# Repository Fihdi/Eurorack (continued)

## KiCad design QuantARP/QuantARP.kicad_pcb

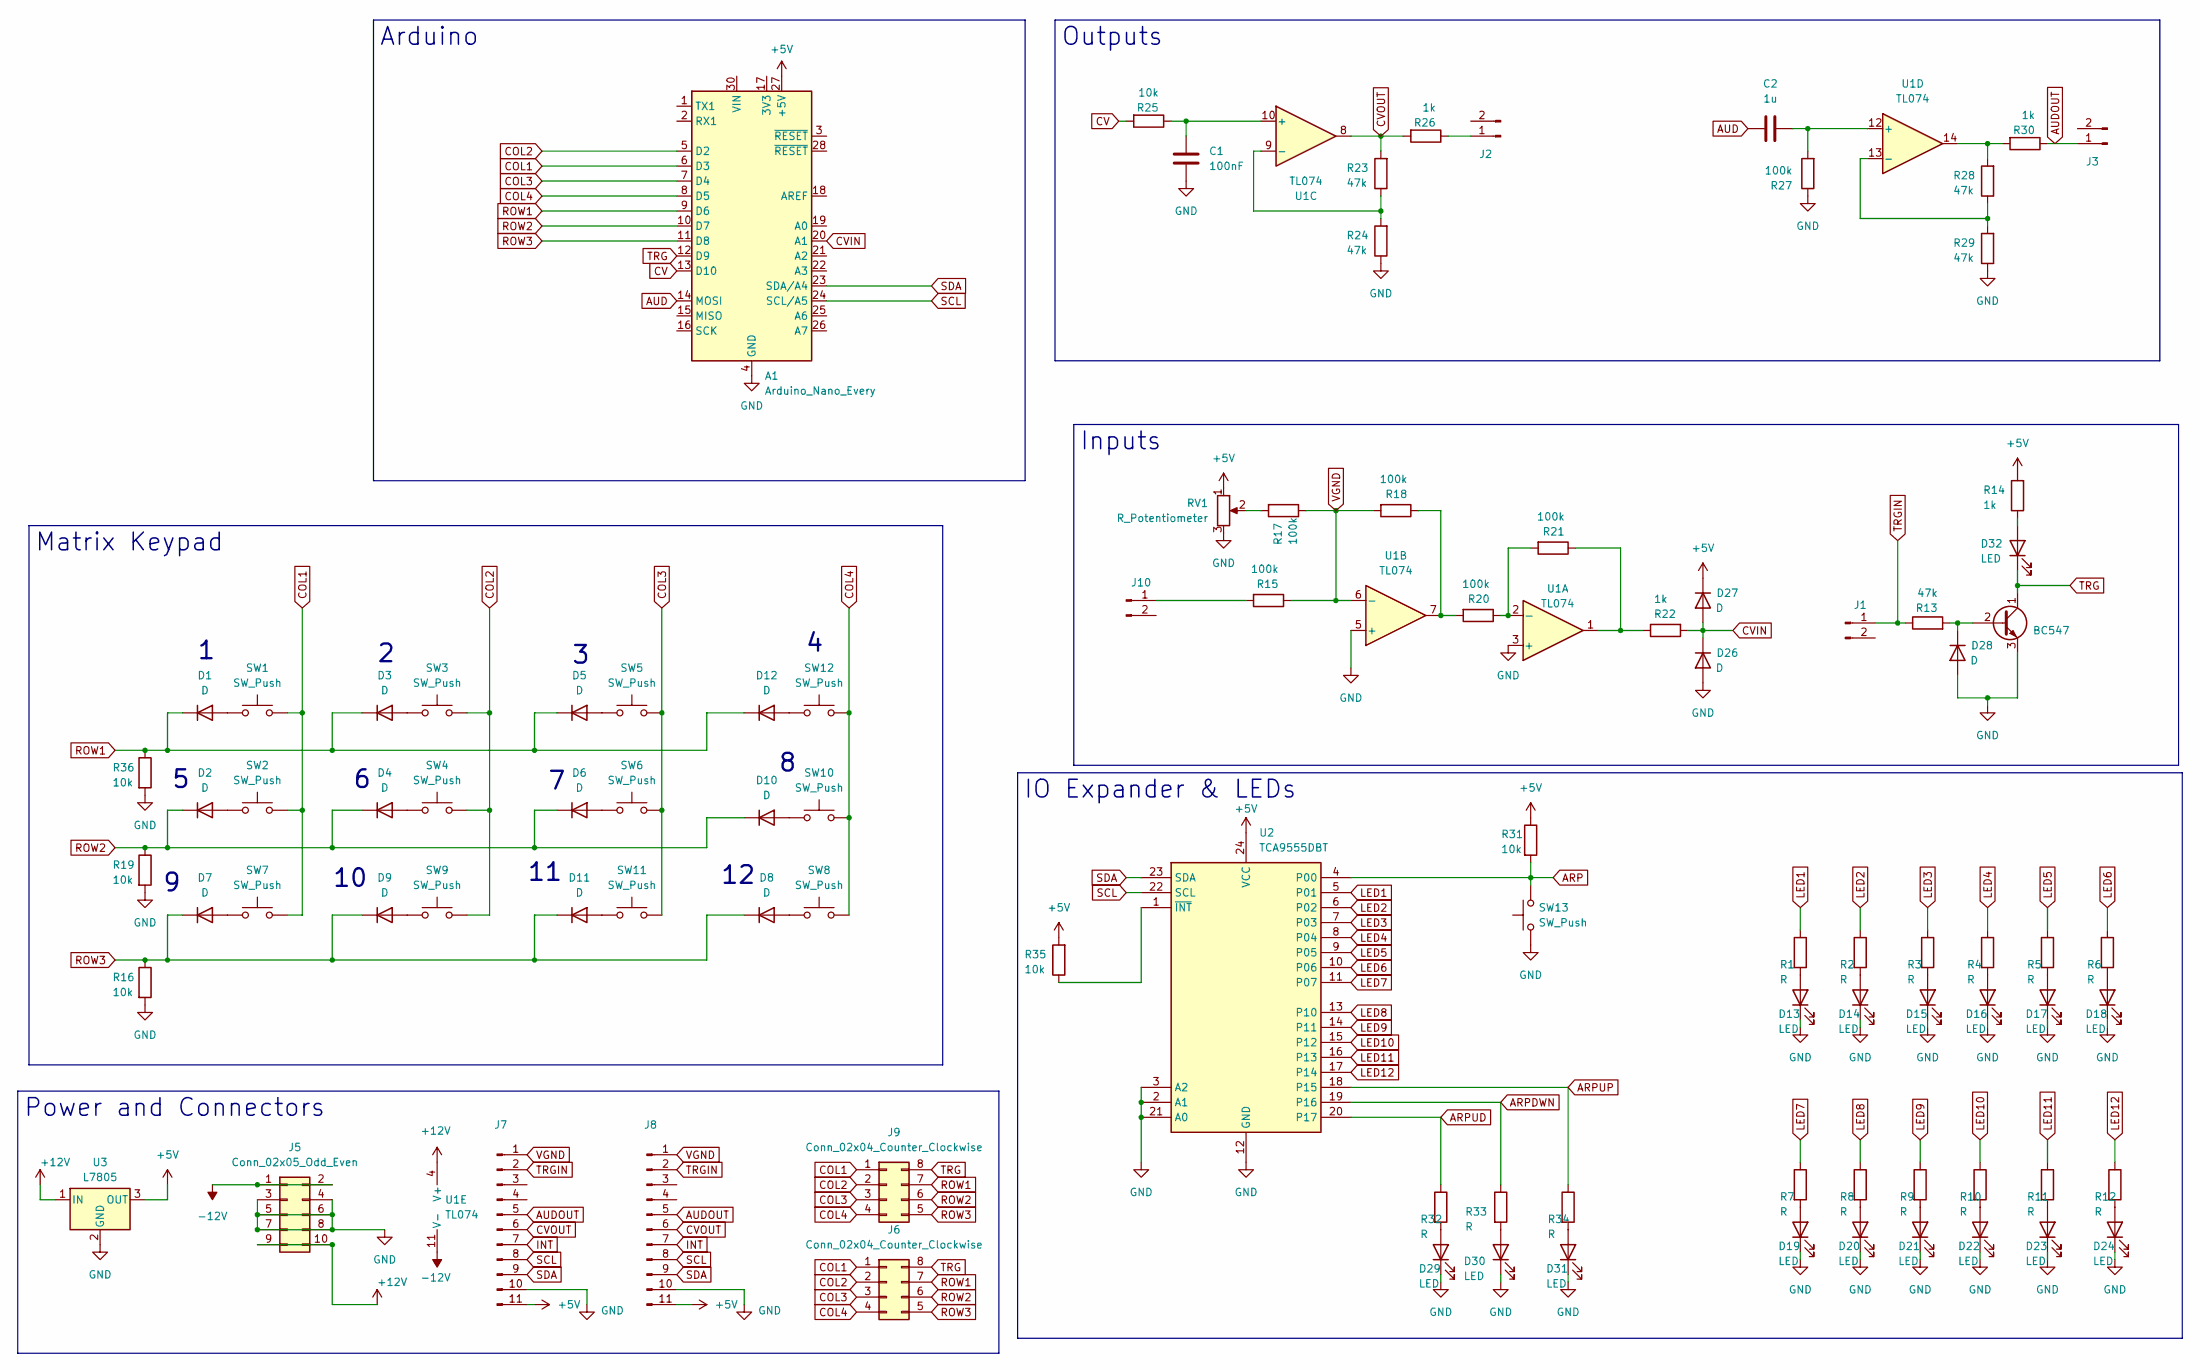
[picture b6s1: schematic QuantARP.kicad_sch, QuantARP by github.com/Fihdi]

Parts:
A1: Arduino_Nano_Every; Arduino_Nano
C1: 100nF; C_Disc_D7.0mm_W2.5mm_P5.00mm
C2: 1u; C_Disc_D7.0mm_W2.5mm_P5.00mm
D1, D2, D3, D4, D5, D6, D7, D8, D9, D10, D11, D12: D; D_SOD-323_HandSoldering
D13, D14, D15, D16, D17, D18, D19, D20, D21, D22, D23, D24, D29, D30, D31, D32: LED; LED_D3.0mm
D26, D27, D28: D; D_1206_3216Metric
J1, J2, J3, J10: Conn_01x02_Pin; 3mm5 Mono Aux
J5: Conn_02x05_Odd_Even; IDC-Header_2x05_P2.54mm_Vertical
J6, J9: Conn_02x04_Counter_Clockwise; IDC-Header_2x04_P2.54mm_Vertical
J7, J8: Conn_01x11_Pin; PinSocket_1x11_P2.54mm_Vertical
Q9: BC547; TO-92_Inline_Wide
R1, R2, R3, R4, R5, R6, R7, R8, R9, R10, R11, R12: R; R_1206_3216Metric
R13, R23, R24, R28, R29: 47k; R_Axial_DIN0207_L6.3mm_D2.5mm_P7.62mm_Horizontal
R14, R22, R26, R30: 1k; R_Axial_DIN0207_L6.3mm_D2.5mm_P7.62mm_Horizontal
R15, R17, R18, R20, R21, R27: 100k; R_Axial_DIN0207_L6.3mm_D2.5mm_P7.62mm_Horizontal
R16, R19, R25, R31, R35, R36: 10k; R_Axial_DIN0207_L6.3mm_D2.5mm_P7.62mm_Horizontal
R32, R33, R34: R; R_Axial_DIN0207_L6.3mm_D2.5mm_P7.62mm_Horizontal
RV1: R_Potentiometer; Potentiometer_Bourns_PTV09A-1_Single_Vertical
SW1, SW2, SW3, SW4, SW5, SW6, SW7, SW8, SW9, SW10, SW11, SW12, SW13: SW_Push; PushButton
U1: TL074; DIP-14_W7.62mm
U2: TCA9555DBT; SSOP-24_5.3x8.2mm_P0.65mm
U3: L7805; TO-252-3_TabPin2

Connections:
+5V: A1.27 (+5V), D27.1 (K), J7.11, J8.11, R14.2, R31.1, R35.2, RV1.1, U2.24 (VCC), U3.3 (OUT)
+12V: J5.9, J5.10, U1.4 (V+), U3.1 (IN)
-12V: J5.1, J5.2, U1.11 (V-)
ARP: R31.2, SW13.2, U2.4 (P00)
ARPDWN: R33.1, U2.19 (P16)
ARPUD: R32.1, U2.20 (P17)
ARPUP: R34.1, U2.18 (P15)
AUD: A1.14 (MOSI), C2.1
AUDOUT: J3.1, J7.5, J8.5, R30.1
COL1: A1.6 (D3), J6.1, J9.1, SW1.2, SW2.2, SW7.2
COL2: A1.5 (D2), J6.2, J9.2, SW3.2, SW4.2, SW9.2
COL3: A1.7 (D4), J6.3, J9.3, SW5.2, SW6.2, SW11.2
COL4: A1.8 (D5), J6.4, J9.4, SW8.2, SW10.2, SW12.2
CV: A1.13 (D10), R25.2
CVIN: A1.20 (A1), D26.1 (K), D27.2 (A), R22.2
CVOUT: J7.6, J8.6, R23.2, R26.2, U1.8
GND: A1.4 (GND), A1.29 (GND), C1.2, D13.1 (K), D14.1 (K), D15.1 (K), D16.1 (K), D17.1 (K), D18.1 (K), D19.1 (K), D20.1 (K), D21.1 (K), D22.1 (K), D23.1 (K), D24.1 (K), D26.2 (A), D28.2 (A), D29.1 (K), D30.1 (K), D31.1 (K), J5.3, J5.4, J5.5, J5.6, J5.7, J5.8, J7.10, J8.10, Q9.3 (E), R16.2, R19.2, R24.1, R27.1, R29.1, R36.2, RV1.3, SW13.1, U1.3 (+), U1.5 (+), U2.2 (A1), U2.3 (A2), U2.12 (GND), U2.21 (A0), U3.2 (GND)
INT: J7.7, J8.7
LED1: R1.1, U2.5 (P01)
LED2: R2.1, U2.6 (P02)
LED3: R3.1, U2.7 (P03)
LED4: R4.1, U2.8 (P04)
LED5: R5.1, U2.9 (P05)
LED6: R6.1, U2.10 (P06)
LED7: R7.1, U2.11 (P07)
LED8: R8.1, U2.13 (P10)
LED9: R9.1, U2.14 (P11)
LED10: R10.1, U2.15 (P12)
LED11: R11.1, U2.16 (P13)
LED12: R12.1, U2.17 (P14)
unnamed: D1.2 (A), SW1.1
unnamed: D2.2 (A), SW2.1
unnamed: D3.2 (A), SW3.1
unnamed: D4.2 (A), SW4.1
unnamed: D5.2 (A), SW5.1
unnamed: D6.2 (A), SW6.1
unnamed: D7.2 (A), SW7.1
unnamed: D8.2 (A), SW8.1
unnamed: D9.2 (A), SW9.1
unnamed: D10.2 (A), SW10.1
unnamed: D11.2 (A), SW11.1
unnamed: D12.2 (A), SW12.1
unnamed: D13.2 (A), R1.2
unnamed: D14.2 (A), R2.2
unnamed: D15.2 (A), R3.2
unnamed: D16.2 (A), R4.2
unnamed: D17.2 (A), R5.2
unnamed: D18.2 (A), R6.2
unnamed: D19.2 (A), R7.2
unnamed: D20.2 (A), R8.2
unnamed: D21.2 (A), R9.2
unnamed: D22.2 (A), R10.2
unnamed: D23.2 (A), R11.2
unnamed: D24.2 (A), R12.2
unnamed: D28.1 (K), Q9.2 (B), R13.2
unnamed: D29.2 (A), R32.2
unnamed: D30.2 (A), R33.2
unnamed: D31.2 (A), R34.2
unnamed: D32.2 (A), R14.1
unnamed: J2.1, R26.1
unnamed: J10.1, R15.2
unnamed: R17.2, RV1.2
unnamed: R18.1, R20.2, U1.7
unnamed: R21.1, R22.1, U1.1
unnamed: R28.2, R30.2, U1.14
unnamed: R20.1, R21.2, U1.2 (-)
unnamed: C1.1, R25.1, U1.10 (+)
unnamed: R23.1, R24.2, U1.9 (-)
unnamed: C2.2, R27.2, U1.12 (+)
unnamed: R28.1, R29.2, U1.13 (-)
unnamed: R35.1, U2.1 (~INT)
ROW1: A1.9 (D6), D1.1 (K), D3.1 (K), D5.1 (K), D12.1 (K), J6.7, J9.7, R36.1
ROW2: A1.10 (D7), D2.1 (K), D4.1 (K), D6.1 (K), D10.1 (K), J6.6, J9.6, R19.1
ROW3: A1.11 (D8), D7.1 (K), D8.1 (K), D9.1 (K), D11.1 (K), J6.5, J9.5, R16.1
TRG: A1.12 (D9), D32.1 (K), J6.8, J9.8, Q9.1 (C)
TRGIN: J1.1, J7.2, J8.2, R13.1
VGND: J7.1, J8.1, R15.1, R17.1, R18.2, U1.6 (-)

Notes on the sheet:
Matrix Keypad
Power and Connectors
Outputs
IO Expander & LEDs
Arduino
Inputs

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
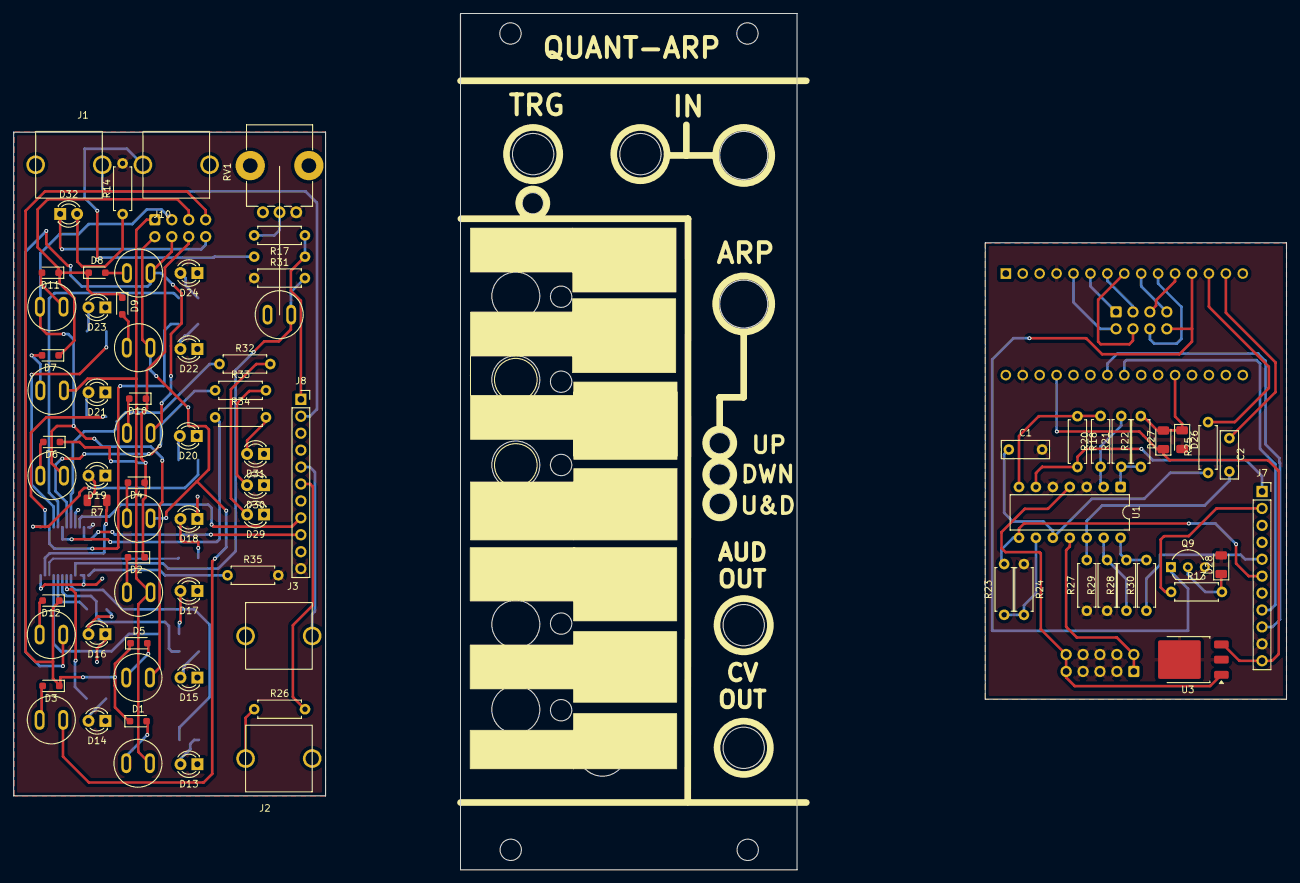
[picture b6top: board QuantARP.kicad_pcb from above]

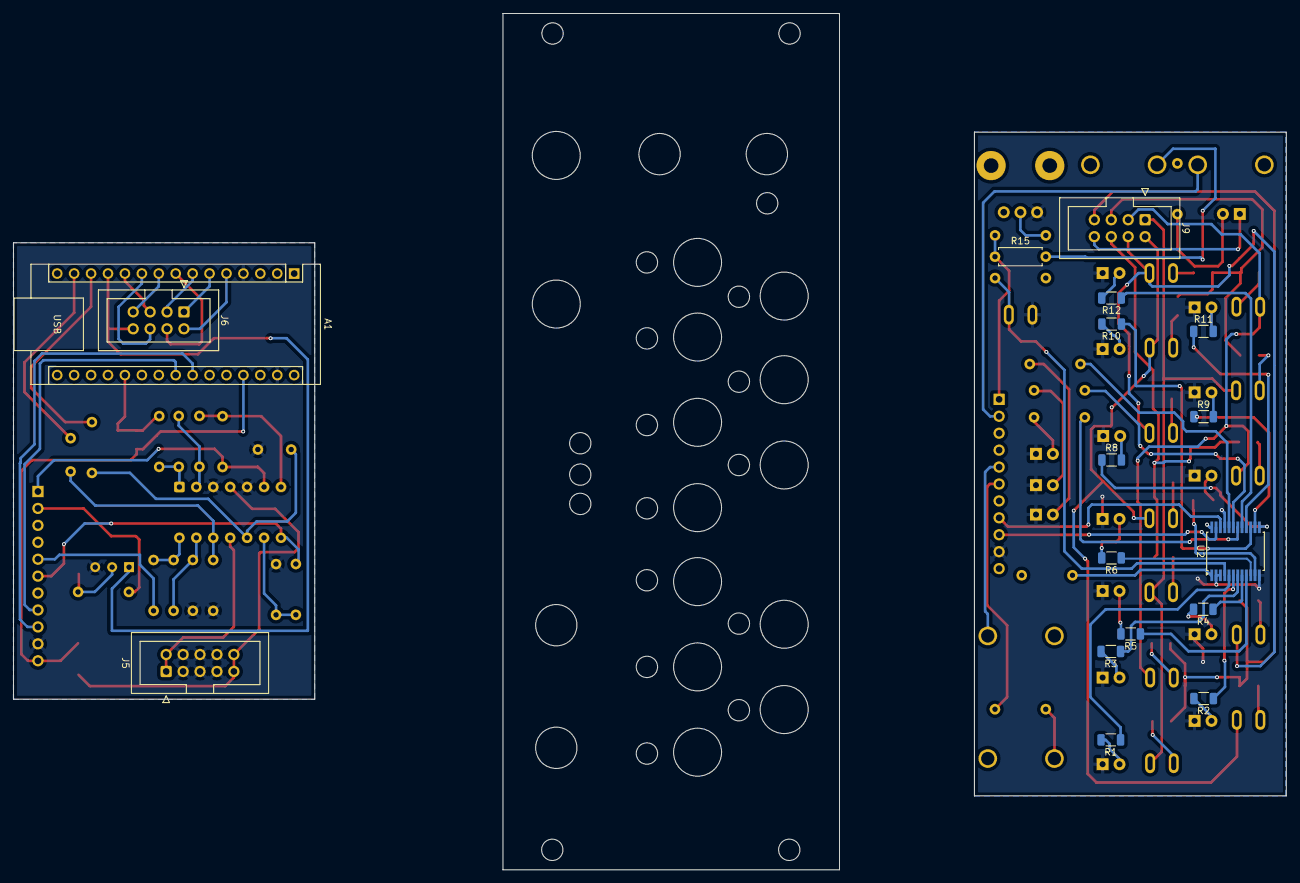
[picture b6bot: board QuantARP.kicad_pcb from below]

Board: 2 copper layers, 191.0 x 128.5 mm, 94 parts (17 on the bottom side), 79 nets.

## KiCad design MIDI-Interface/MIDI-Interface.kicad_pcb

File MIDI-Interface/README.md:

# 8 Channel MIDI interface module in 8hp

MIDI Interface module with 5-Pin MIDI input and with 4 CV and 4 Gate/Trigger outputs. It lets you control other modules with MIDI Controllers or DAWs.

CV channels are mapped to MIDI CC number 20, 21, 22 and 23.

# Expansion

To expand module to 16 channels, the Pin beneath the TL072 can be used to connect two MIDI-INT Modules together. Leave the TL072 unpopulated on the second module and upload MIDI-INT-EXP.ino into the Arduino Nano.

CV channels for the expansion module are mapped to MIDI CC numbers 24, 25, 26 and 27.

Module is inspired by CircuitsAndSounds AutomationSequencer Project and is similar to an Univer Inter from Noise Engineering

https://github.com/CircuitsAndSounds/MIDIAutomationSequencer

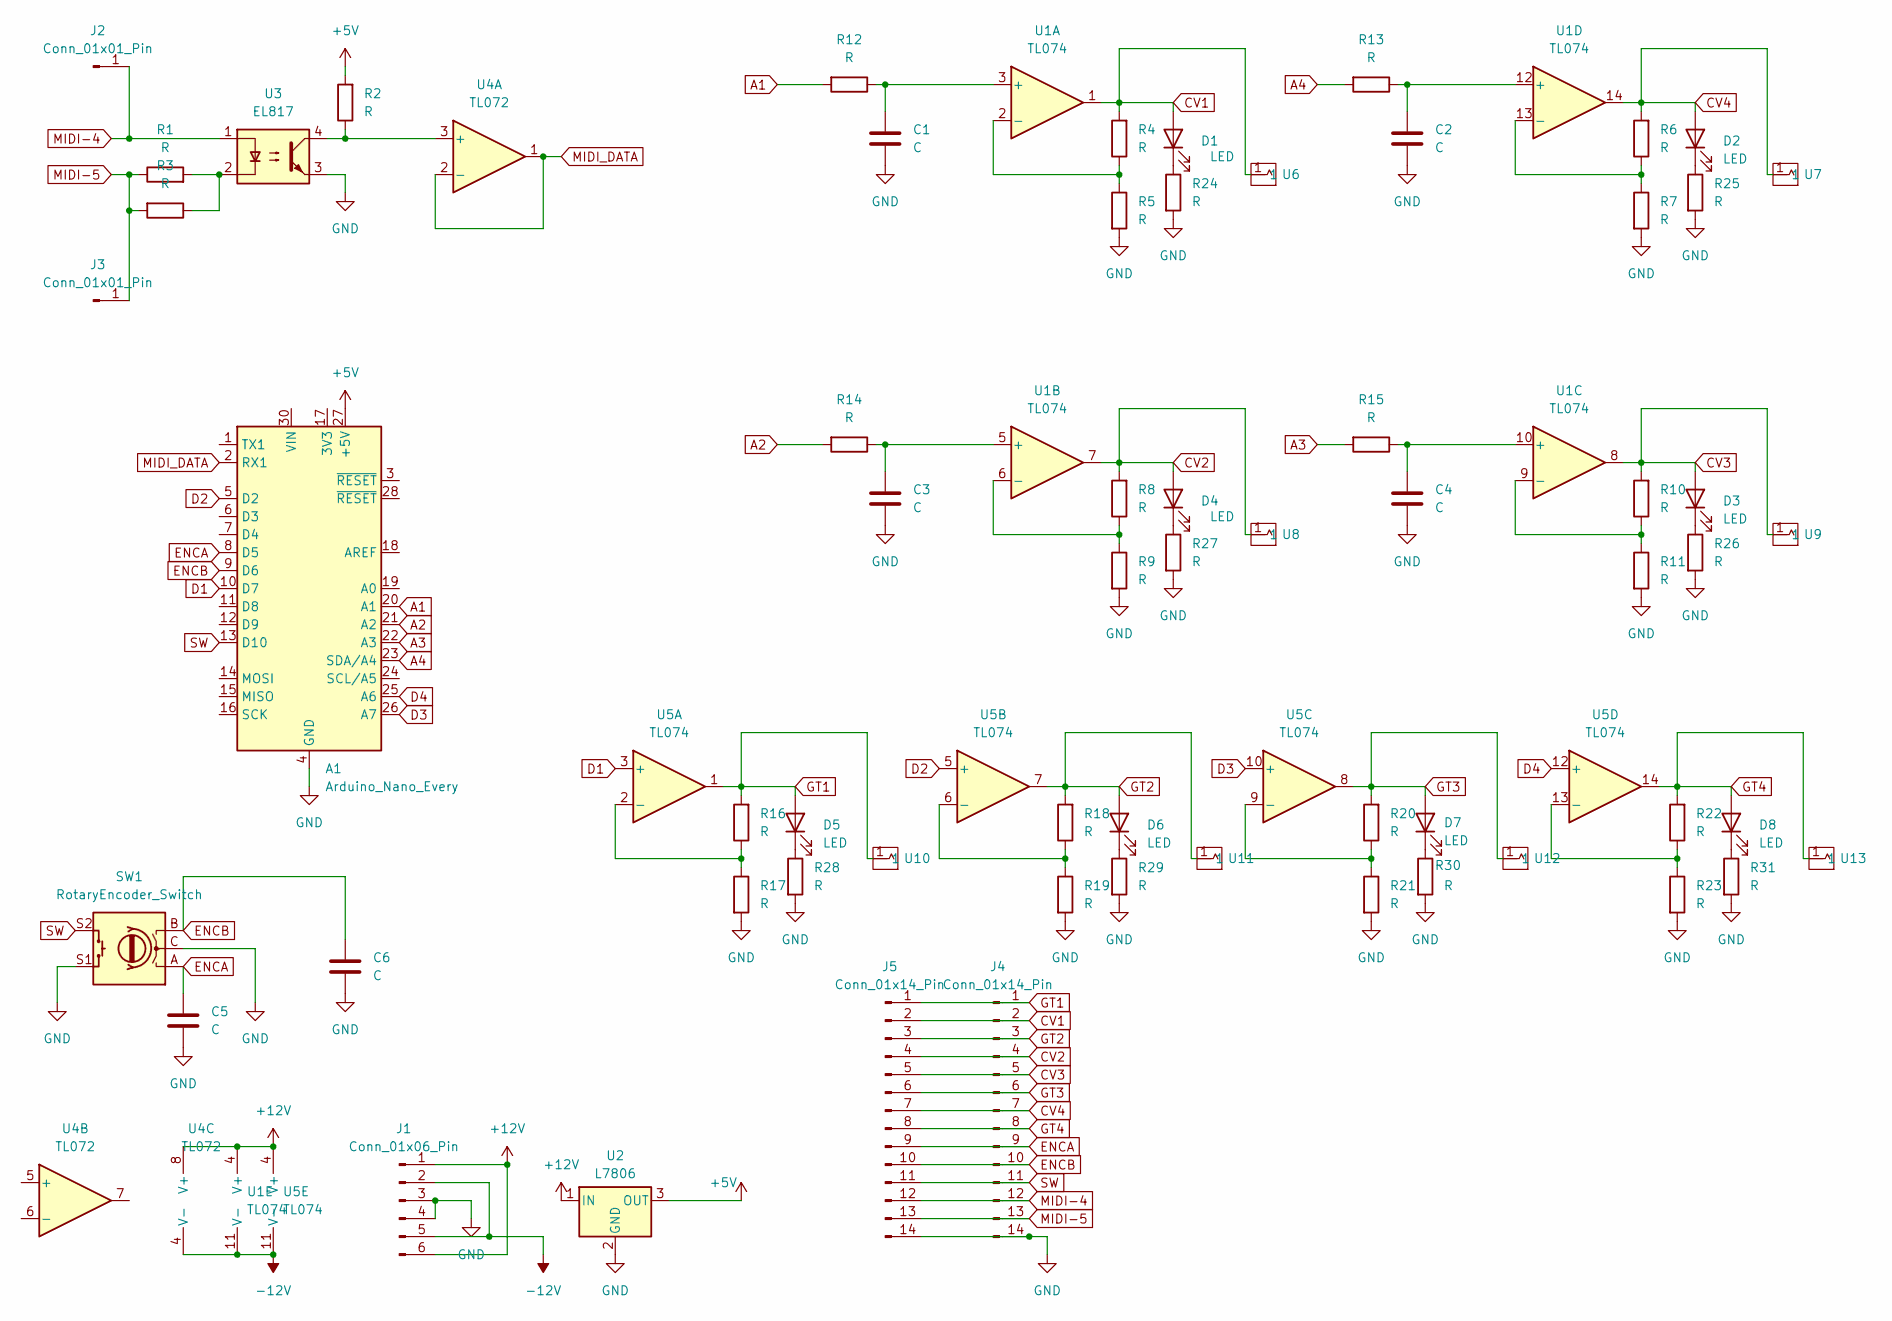
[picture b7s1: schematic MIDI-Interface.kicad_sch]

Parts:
A1: Arduino_Nano_Every; Arduino_Nano
C1, C2, C3, C4, C5, C6: C; C_Rect_L7.0mm_W2.5mm_P5.00mm
D1, D2, D3, D4, D5, D6, D7, D8: LED; LED_D3.0mm
J1: Conn_01x06_Pin; PinSocket_1x06_P2.54mm_Vertical
J2, J3: Conn_01x01_Pin; PinHeader_1x01_P2.54mm_Vertical
J4, J5: Conn_01x14_Pin; PinHeader_1x14_P2.54mm_Vertical
R1, R2, R3, R4, R5, R6, R7, R8, R9, R10, R11, R12, R13, R14, R15, R16, R17, R18, R19, R20, R21, R22, R23, R24, R25, R26, R27, R28, R29, R30, R31: R; R_Axial_DIN0207_L6.3mm_D2.5mm_P7.62mm_Horizontal
SW1: RotaryEncoder_Switch; RotaryEncoder_Alps_EC11E-Switch_Vertical_H20mm
U1: TL074; DIP-14_W7.62mm_Socket
U2: L7806; TO-252-3_TabPin2
U3: EL817; DIP-4_W7.62mm
U4: TL072; DIP-8_W7.62mm
U5: TL074; DIP-14_W7.62mm
U6, U7, U8, U9, U10, U11, U12, U13: Aux_flush; 3mm5 Mono Aux

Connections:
+5V: A1.27 (+5V), R2.2, U2.3 (OUT)
+12V: J1.1, J1.6, U1.4 (V+), U2.1 (IN), U4.8 (V+), U5.4 (V+)
-12V: J1.2, J1.5, U1.11 (V-), U4.4 (V-), U5.11 (V-)
A1: A1.20 (A1), R12.2
A2: A1.21 (A2), R14.2
A3: A1.22 (A3), R15.2
A4: A1.23 (SDA/A4), R13.2
CV1: D1.2 (A), J4.2, J5.2, R4.2, U1.1, U6.1
CV2: D4.2 (A), J4.4, J5.4, R8.2, U1.7, U8.1
CV3: D3.2 (A), J4.5, J5.5, R10.2, U1.8, U9.1
CV4: D2.2 (A), J4.7, J5.7, R6.2, U1.14, U7.1
D1: A1.10 (D7), U5.3 (+)
D2: A1.5 (D2), U5.5 (+)
D3: A1.26 (A7), U5.10 (+)
D4: A1.25 (A6), U5.12 (+)
ENCA: A1.8 (D5), C5.1, J4.9, J5.9, SW1.A
ENCB: A1.9 (D6), C6.1, J4.10, J5.10, SW1.B
GND: A1.4 (GND), A1.29 (GND), C1.2, C2.2, C3.2, C4.2, C5.2, C6.2, J1.3, J1.4, J4.14, J5.14, R5.2, R7.2, R9.2, R11.2, R17.2, R19.2, R21.2, R23.2, R24.2, R25.2, R26.2, R27.2, R28.2, R29.2, R30.2, R31.2, SW1.C, SW1.S1, U2.2 (GND), U3.3
GT1: D5.2 (A), J4.1, J5.1, R16.2, U5.1, U10.1
GT2: D6.2 (A), J4.3, J5.3, R18.2, U5.7, U11.1
GT3: D7.2 (A), J4.6, J5.6, R20.2, U5.8, U12.1
GT4: D8.2 (A), J4.8, J5.8, R22.2, U5.14, U13.1
MIDI-4: J2.1, J4.12, J5.12, U3.1
MIDI-5: J3.1, J4.13, J5.13, R1.1, R3.2
MIDI_DATA: A1.2 (RX1), U4.1, U4.2 (-)
unnamed: D1.1 (K), R24.1
unnamed: D2.1 (K), R25.1
unnamed: D3.1 (K), R26.1
unnamed: D4.1 (K), R27.1
unnamed: D5.1 (K), R28.1
unnamed: D6.1 (K), R29.1
unnamed: D7.1 (K), R30.1
unnamed: D8.1 (K), R31.1
unnamed: R1.2, R3.1, U3.2
unnamed: C1.1, R12.1, U1.3 (+)
unnamed: R4.1, R5.1, U1.2 (-)
unnamed: C3.1, R14.1, U1.5 (+)
unnamed: R8.1, R9.1, U1.6 (-)
unnamed: C4.1, R15.1, U1.10 (+)
unnamed: R10.1, R11.1, U1.9 (-)
unnamed: C2.1, R13.1, U1.12 (+)
unnamed: R6.1, R7.1, U1.13 (-)
unnamed: R2.1, U3.4, U4.3 (+)
unnamed: R16.1, R17.1, U5.2 (-)
unnamed: R18.1, R19.1, U5.6 (-)
unnamed: R20.1, R21.1, U5.9 (-)
unnamed: R22.1, R23.1, U5.13 (-)
SW: A1.13 (D10), J4.11, J5.11, SW1.S2

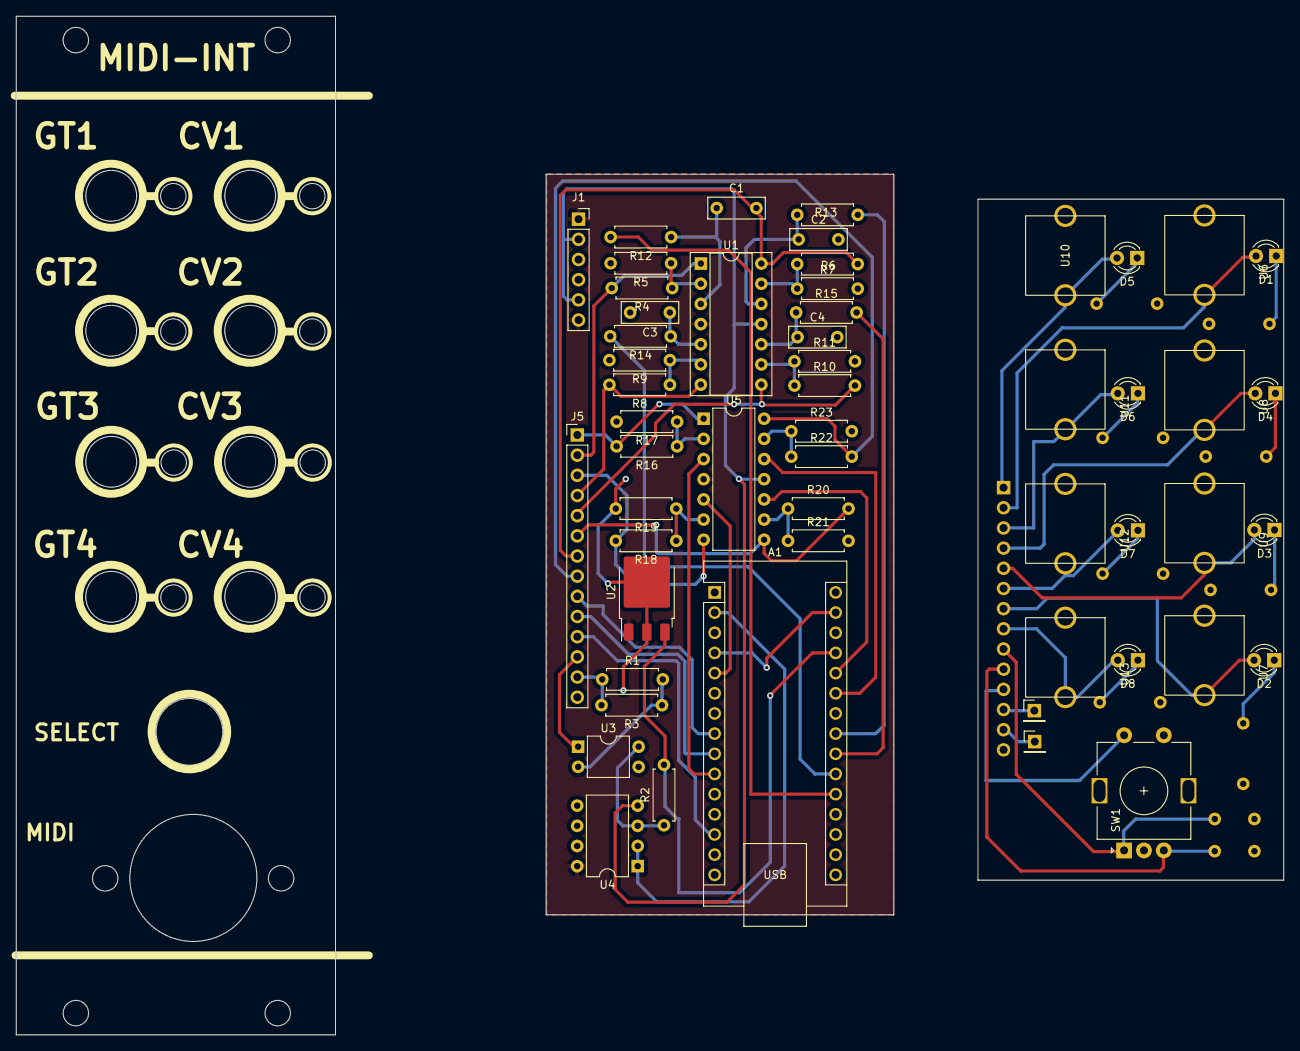
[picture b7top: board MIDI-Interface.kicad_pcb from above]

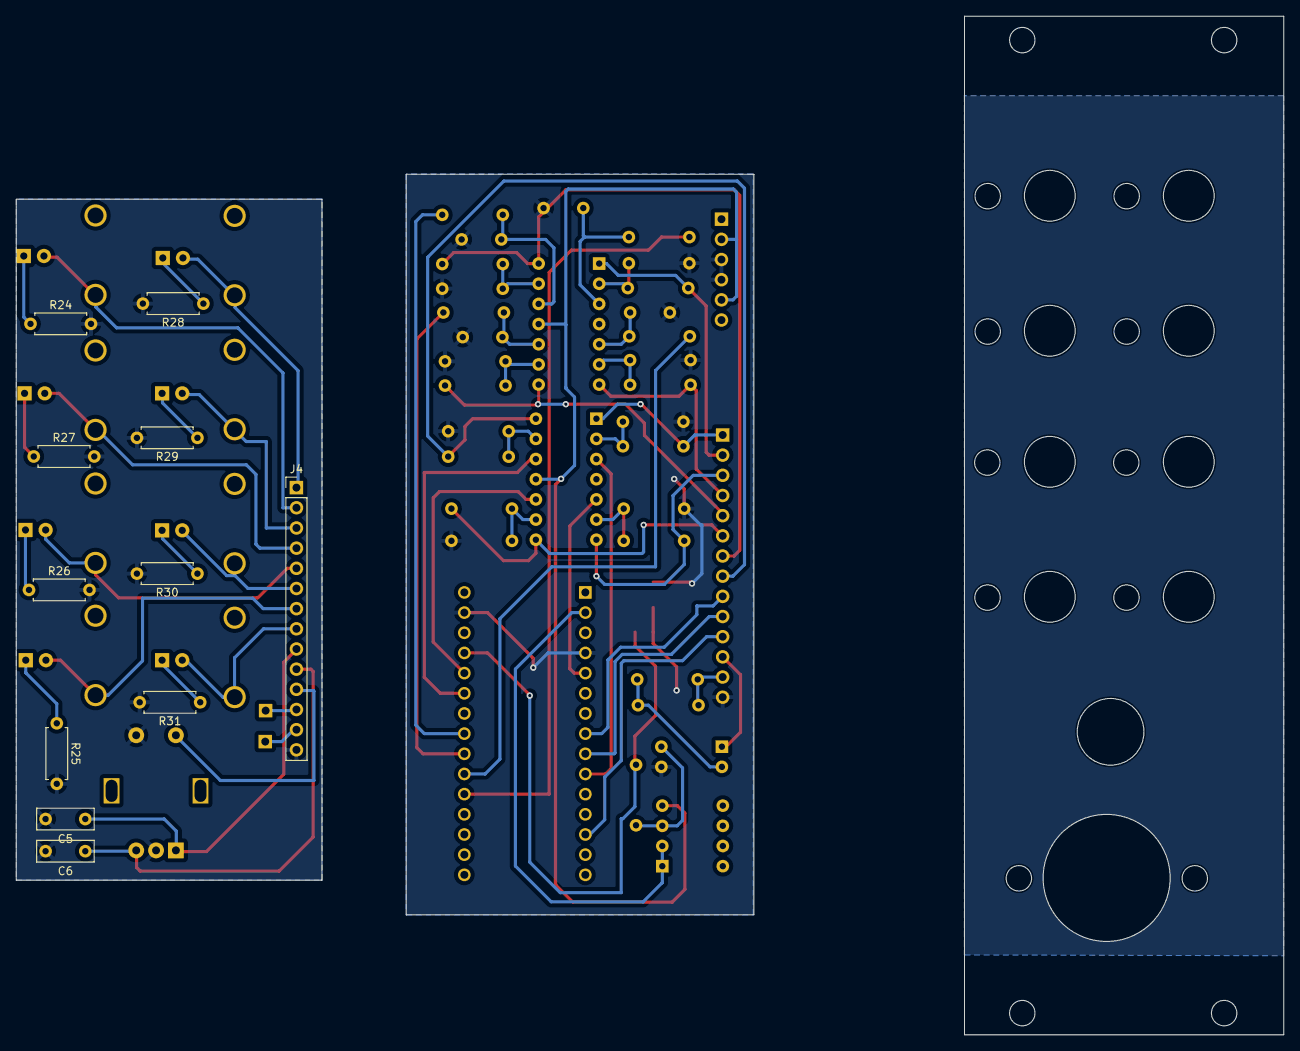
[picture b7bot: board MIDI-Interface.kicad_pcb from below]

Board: 2 copper layers, 159.6 x 128.2 mm, 65 parts (11 on the bottom side), 48 nets.

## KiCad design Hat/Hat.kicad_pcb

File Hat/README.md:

# 8hp Hi-Hat module

Snare / Hi Hat module with CV control over the decay Time.

Known Issue: The top part of this module should be a random voltage generator whose signal can be used to control the decay time, this does not work as of right now.

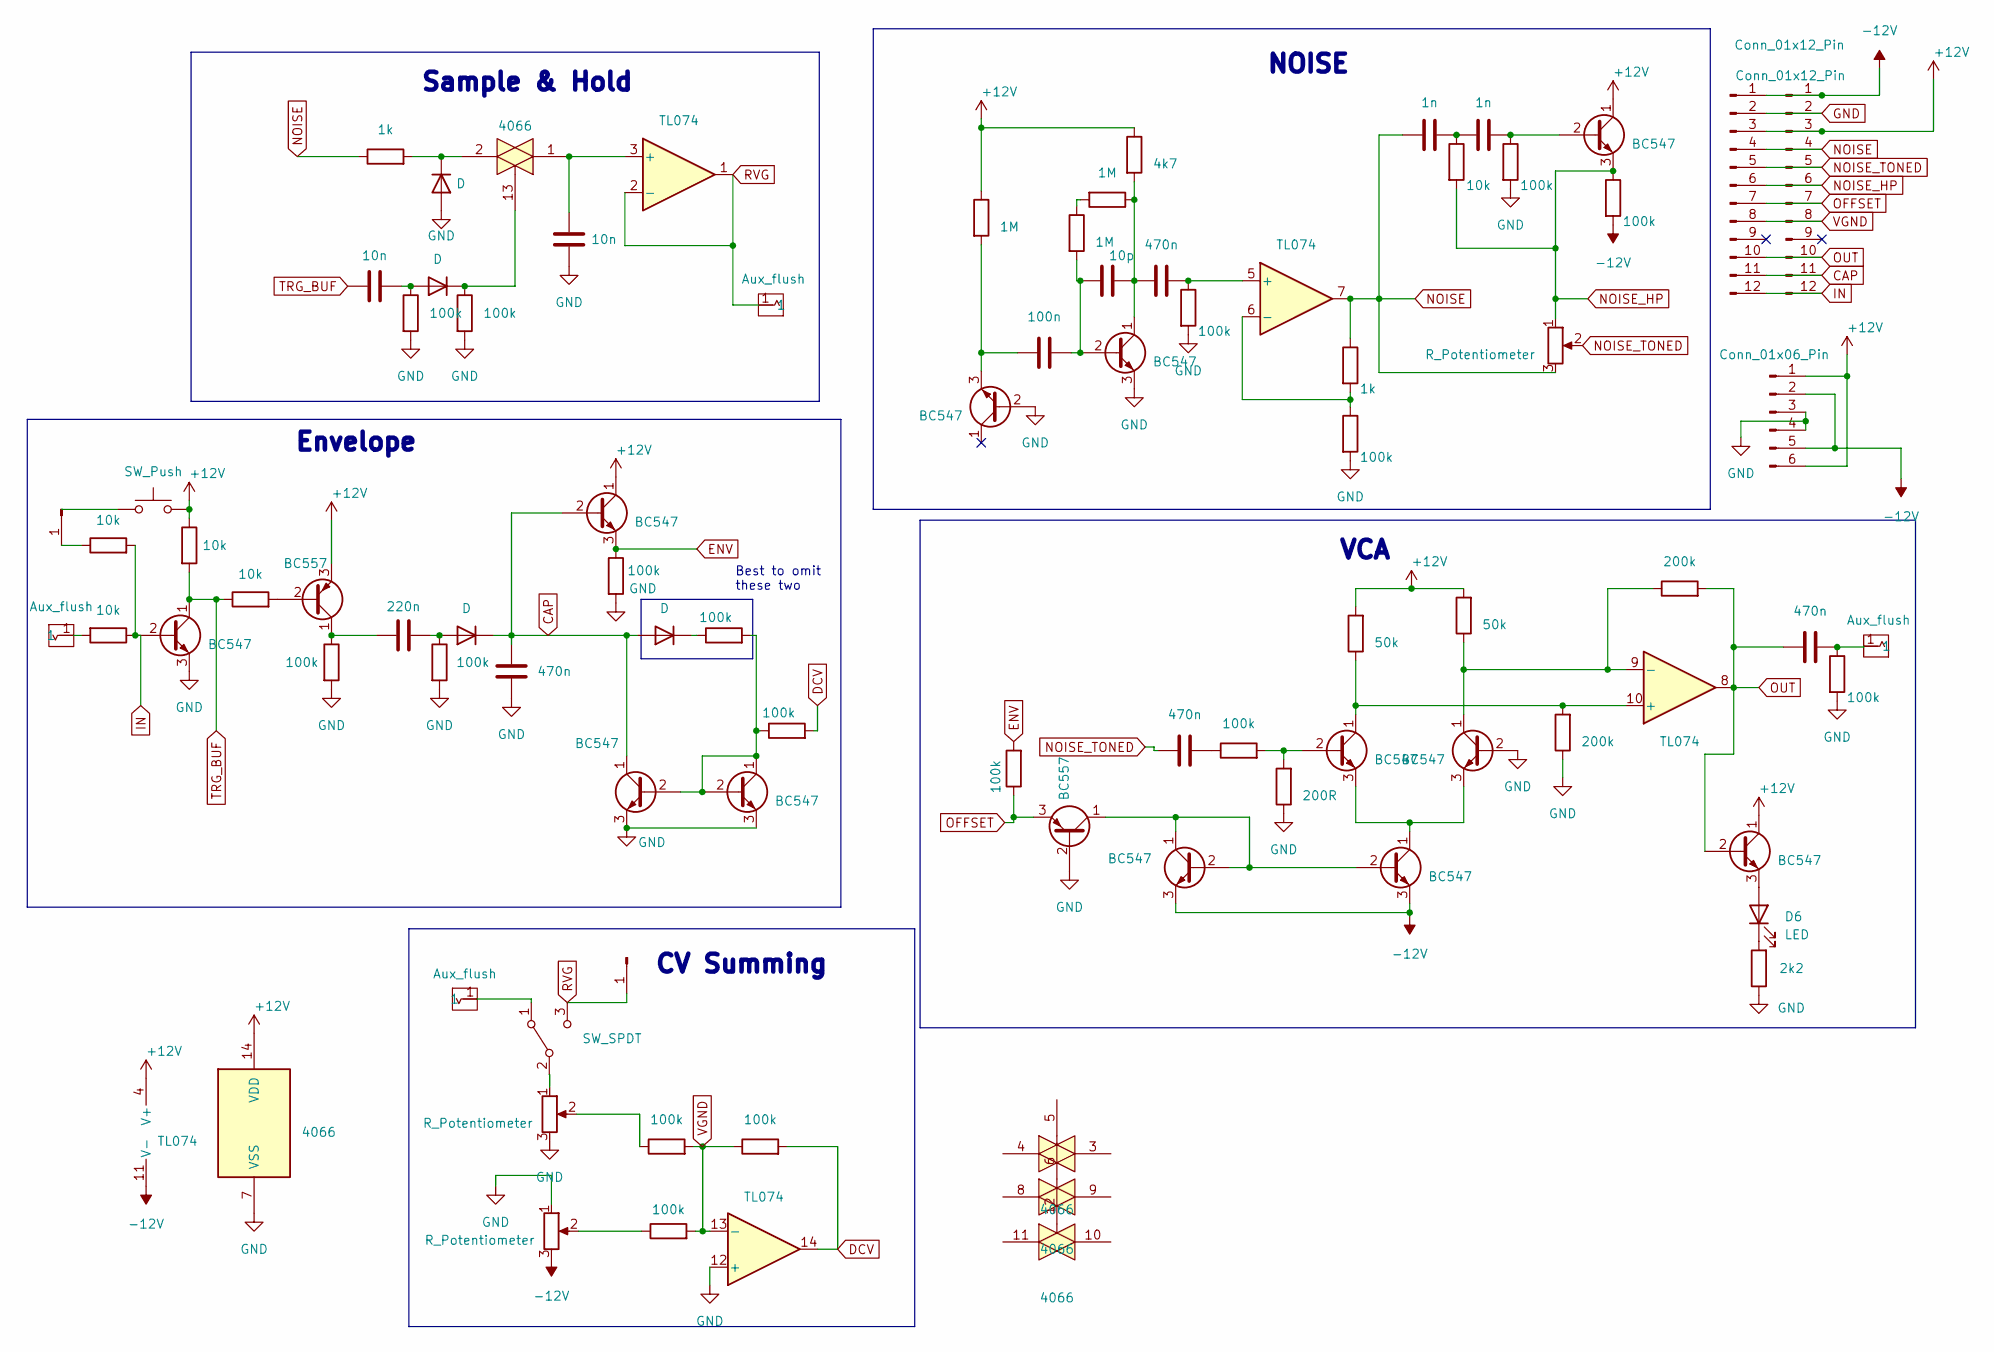
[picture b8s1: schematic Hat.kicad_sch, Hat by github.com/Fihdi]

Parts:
C1: 220n; C_Axial_L3.8mm_D2.6mm_P7.50mm_Horizontal
C2, C5, C10, C11: 470n; C_Axial_L3.8mm_D2.6mm_P7.50mm_Horizontal
C3: 100n; C_Axial_L3.8mm_D2.6mm_P7.50mm_Horizontal
C4: 10p; C_Axial_L3.8mm_D2.6mm_P7.50mm_Horizontal
C6, C7: 1n; C_Axial_L3.8mm_D2.6mm_P7.50mm_Horizontal
C8, C9: 10n; C_Axial_L3.8mm_D2.6mm_P7.50mm_Horizontal
D1, D2, D3, D5: D; D_A-405_P5.08mm_Vertical_AnodeUp
D6: LED; LED_D5.0mm
J1, J5: Conn_01x01_Pin; PinHeader_1x01_P2.54mm_Vertical
J2, J3: Conn_01x12_Pin; PinHeader_1x12_P2.54mm_Vertical
J4: Conn_01x06_Pin; PinHeader_1x06_P2.54mm_Vertical
Q1, Q2, Q3, Q6, Q7, Q8, Q9, Q10, Q11, Q13, Q14, Q15: BC547; TO-92_Inline_Wide
Q4, Q12: BC557; TO-92_Inline_Wide
R1, R6, R7, R8, R10, R11, R12, R16, R18, R19, R25, R27, R28, R30, R31, R33, R36: 100k; R_Axial_DIN0204_L3.6mm_D1.6mm_P7.62mm_Horizontal
R2, R3, R4, R5, R29: 10k; R_Axial_DIN0204_L3.6mm_D1.6mm_P7.62mm_Horizontal
R13, R14, R35: 1M; R_Axial_DIN0204_L3.6mm_D1.6mm_P7.62mm_Horizontal
R15: 4k7; R_Axial_DIN0204_L3.6mm_D1.6mm_P7.62mm_Horizontal
R17, R32: 1k; R_Axial_DIN0204_L3.6mm_D1.6mm_P7.62mm_Horizontal
R20: 200R; R_Axial_DIN0204_L3.6mm_D1.6mm_P7.62mm_Horizontal
R21, R22: 50k; R_Axial_DIN0204_L3.6mm_D1.6mm_P7.62mm_Horizontal
R23, R24: 200k; R_Axial_DIN0204_L3.6mm_D1.6mm_P7.62mm_Horizontal
R34: 2k2; R_Axial_DIN0204_L3.6mm_D1.6mm_P7.62mm_Horizontal
RV1, RV2, RV3: R_Potentiometer; AlpsPot
SW1: SW_Push; PushButton
SW2: SW_SPDT; Switch
U1: TL074; DIP-14_W7.62mm_Socket
U2, U4, U6, U7: Aux_flush; 3mm5 Mono Aux
U5: 4066; DIP-14_W10.16mm

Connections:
+12V: J2.3, J3.3, J4.1, J4.6, Q4.3 (E), Q13.1 (C), Q14.1 (C), Q15.1 (C), R4.1, R13.1, R15.1, R21.2, R22.2, SW1.2, U1.4 (V+), U5.14 (VDD)
-12V: J2.1, J3.1, J4.2, J4.5, Q9.3 (E), Q11.3 (E), R27.2, RV1.3, U1.11 (V-)
CAP: C2.2, D1.1 (K), D5.2 (A), J2.11, J3.11, Q1.1 (C), Q14.2 (B)
DCV: R1.2, R11.2, U1.14
ENV: Q14.3 (E), R25.2, R33.1
GND: C2.1, C9.1, D3.2 (A), J2.2, J3.2, J4.3, J4.4, Q1.3 (E), Q2.3 (E), Q3.3 (E), Q6.2 (B), Q7.3 (E), Q10.2 (B), Q12.2 (B), R6.2, R7.2, R16.2, R18.2, R20.1, R23.1, R28.2, R30.2, R31.2, R33.2, R34.1, R36.2, RV1.1, RV2.3, U1.12 (+), U5.7 (VSS)
IN: J2.12, J3.12, Q3.2 (B), R2.2, R3.1
NOISE: C7.1, J2.4, J3.4, R17.1, R32.1, RV3.3, U1.7
NOISE_HP: J2.6, J3.6, Q13.3 (E), R27.1, R29.2, RV3.1
NOISE_TONED: C10.1, J2.5, J3.5, RV3.2
unnamed: C6.1, C7.2, R29.1
unnamed: C10.2, R19.1
unnamed: C11.2, R36.1, U6.1
unnamed: C1.2, D1.2 (A), R7.1
unnamed: C8.2, D2.2 (A), R30.1
unnamed: D2.1 (K), R31.1, U5.13
unnamed: D3.1 (K), R32.2, U5.2
unnamed: D5.1 (K), R8.1
unnamed: D6.2 (A), Q15.3 (E)
unnamed: D6.1 (K), R34.2
unnamed: J1.1, R2.1
unnamed: Q1.2 (B), Q2.1 (C), Q2.2 (B), R1.1, R8.2
unnamed: Q4.2 (B), R5.2
unnamed: C1.1, Q4.1 (C), R6.1
unnamed: C3.1, Q6.3 (E), R13.2
unnamed: C3.2, C4.1, Q7.2 (B), R35.2
unnamed: C4.2, C5.1, Q7.1 (C), R14.1, R15.2
unnamed: Q8.2 (B), R19.2, R20.2
unnamed: Q8.1 (C), R21.1, R23.2, U1.10 (+)
unnamed: Q10.1 (C), R22.1, R24.1, U1.9 (-)
unnamed: Q8.3 (E), Q9.1 (C), Q10.3 (E)
unnamed: Q9.2 (B), Q11.1 (C), Q11.2 (B), Q12.1 (C)
unnamed: C6.2, Q13.2 (B), R28.1
unnamed: R3.2, U2.1
unnamed: R10.1, RV1.2
unnamed: R12.1, RV2.2
unnamed: R14.2, R35.1
unnamed: SW2.1 (A), U4.1
unnamed: RV2.1, SW2.2 (B)
unnamed: C9.2, U1.3 (+), U5.1
unnamed: C5.2, R16.1, U1.5 (+)
unnamed: R17.2, R18.1, U1.6 (-)
OFFSET: J2.7, J3.7, Q12.3 (E), R25.1
OUT: C11.1, J2.10, J3.10, Q15.2 (B), R24.2, U1.8
RVG: J5.1, SW2.3 (C), U1.1, U1.2 (-), U7.1
TRG_BUF: C8.1, Q3.1 (C), R4.2, R5.1
VGND: J2.8, J3.8, R10.2, R11.1, R12.2, U1.13 (-)

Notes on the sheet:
CV Summing
VCA
Envelope
NOISE
Best to omit these two
Sample & Hold

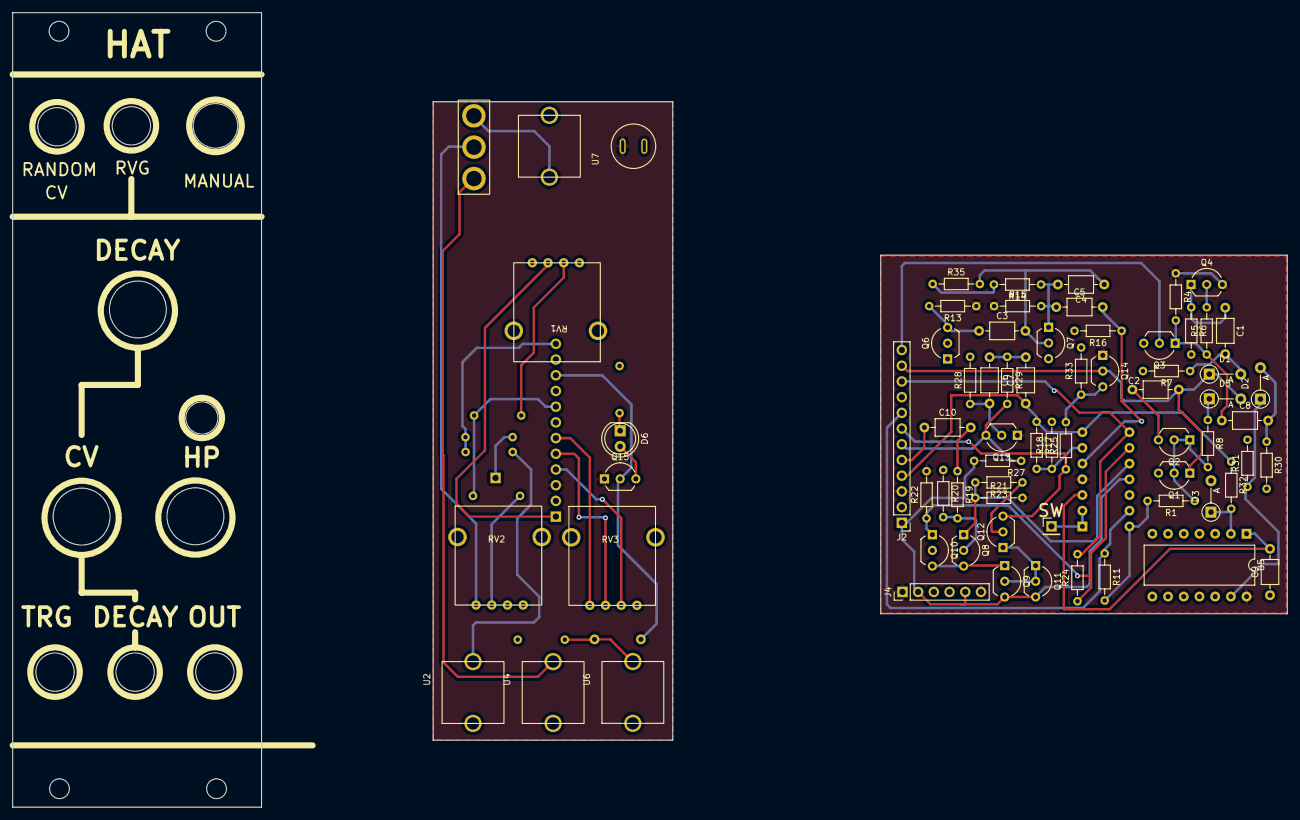
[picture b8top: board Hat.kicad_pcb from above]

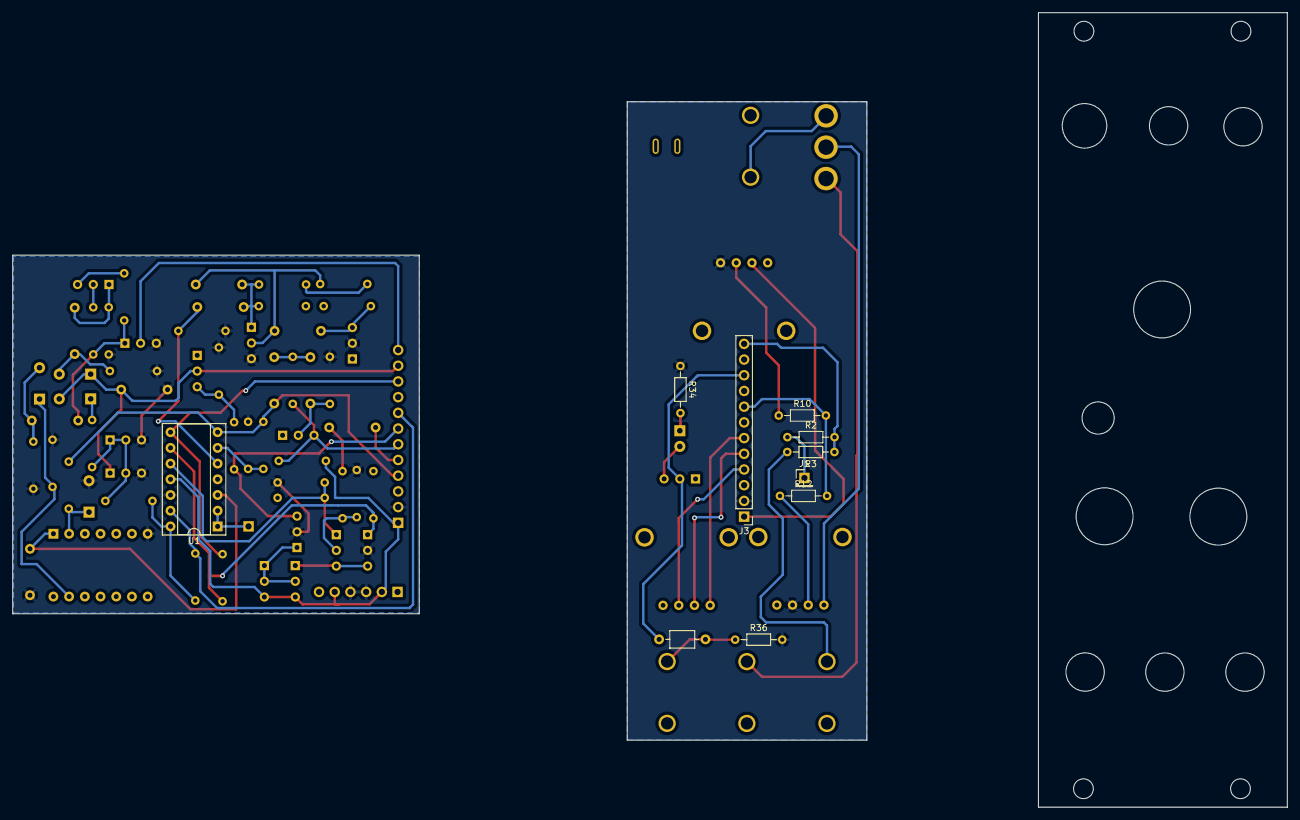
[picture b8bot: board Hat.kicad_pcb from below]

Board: 2 copper layers, 206.1 x 128.5 mm, 80 parts (10 on the bottom side), 47 nets.

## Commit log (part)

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2024-09-24 Rename Euclid.ino to Euclid_InternalOnly.ino
2024-09-26 Update Euclid_DRAFT.ino
    Formatting
2024-09-30 Rename ClockMultiplier.ino to ClockMultiplier_DRAFT.ino
2024-09-30 Add files via upload
    Updated PCB
2024-10-02 Add files via upload
    Minor improvements
2024-10-11 Update MIDI-INT-Draft.ino
    Fixed analogWrites
2024-10-29 Simple Sampler firmware
2024-10-29 Add .gitignore
2024-10-30 Add libDaisy submodule
2024-10-30 Build libDaisy script
2024-10-30 Remove DaisySP, update code to latest libDaisy API
2024-10-30 Documentation: build & flash Daisy module firmware
2024-10-31 Fix clic noise at the end of some samples
2024-11-21 Rename FirstCircuit..PNG to FirstCircuit.PNG
2024-11-22 Move Hardware file with PTAL for reusability
2024-11-22 Move gitignore file to include all firmwares
2024-11-22 add Blink firmware
2024-11-22 Simple sampler firmware documentation
2024-11-22 add TestHardware firmware
2024-11-22 add TestSdCard firmware
2024-11-22 add SynthClave firmware
2024-11-22 Script to build all firmwares
2024-11-22 add firmwares binaries
2024-11-22 Fix readme title
2024-11-22 Gate input GPIO should be configured as NOPULL
2025-05-13 Update README.md
    :)
2025-05-27 Update MIDI-INT-EXP.ino
    Full range of CV. From value to 2*value
2025-05-30 Updated PCB
2025-06-02 ADIOS! LOOK AT LFO2
